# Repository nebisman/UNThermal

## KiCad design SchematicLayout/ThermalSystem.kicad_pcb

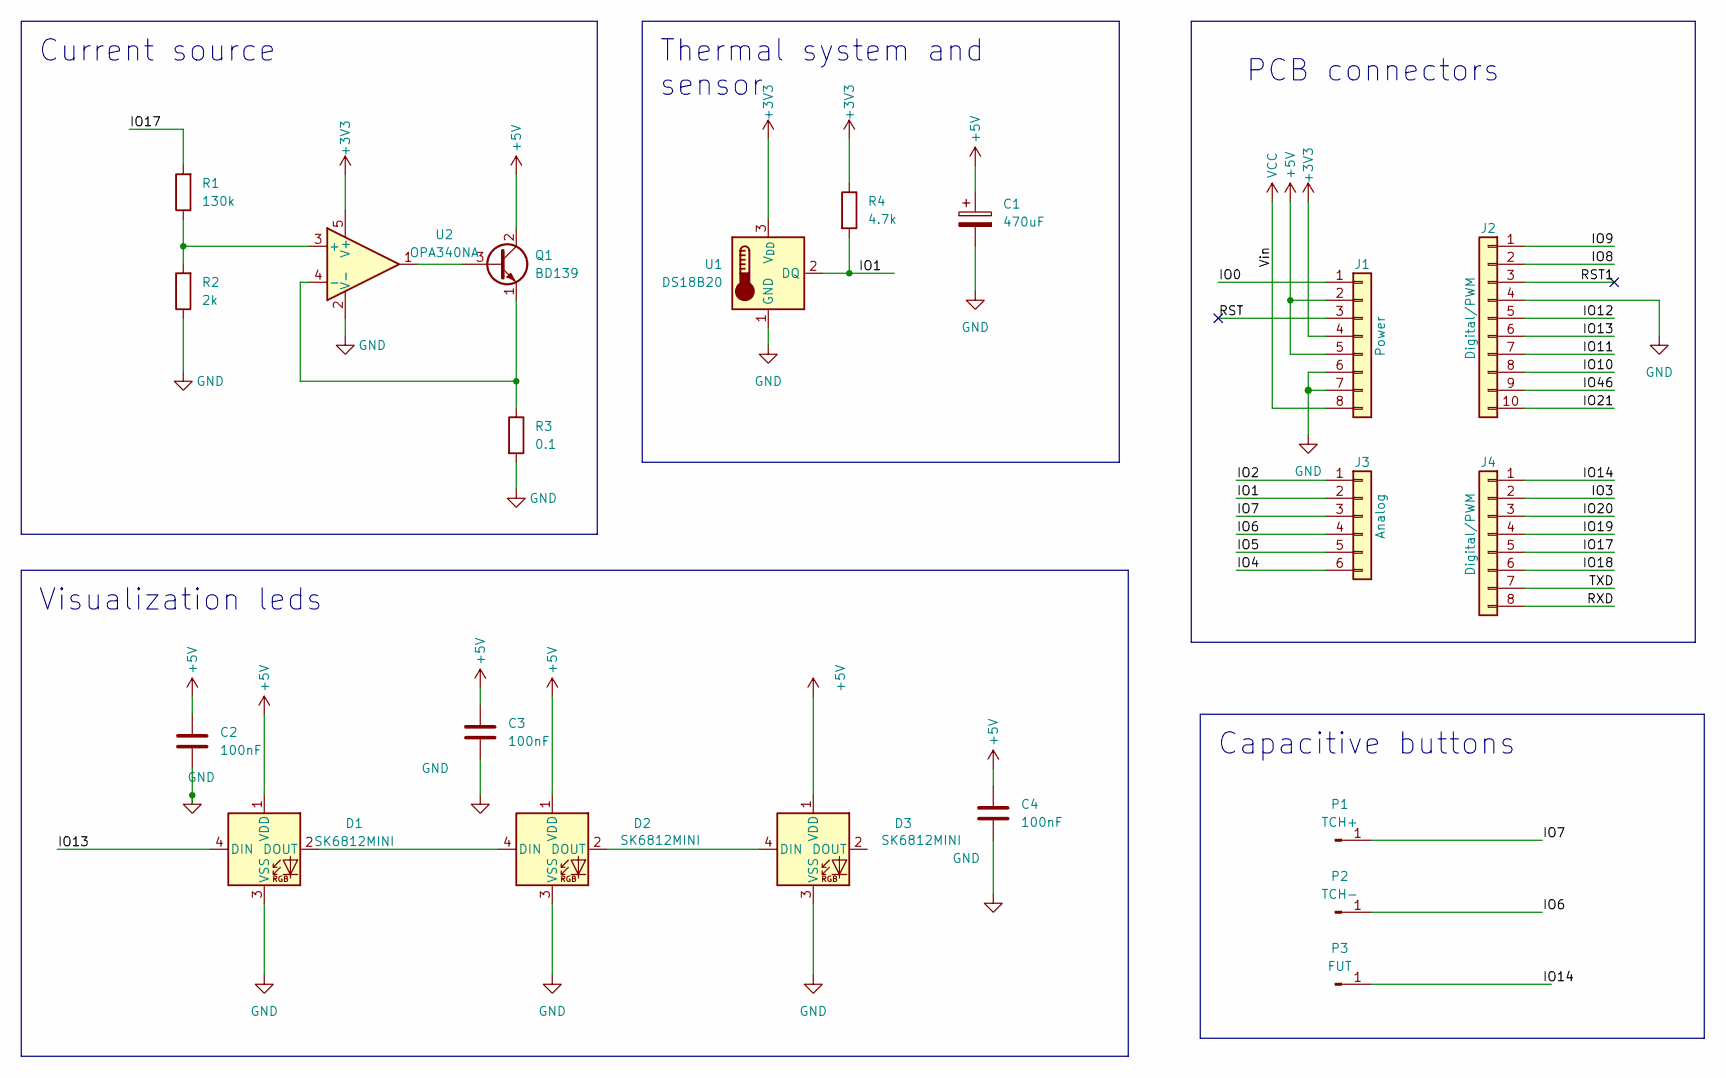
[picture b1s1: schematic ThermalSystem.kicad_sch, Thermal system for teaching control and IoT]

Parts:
C1: 470uF; CP_EIA-7343-30_AVX-N_Pad2.25x2.55mm_HandSolder
C2, C3, C4: 100nF; C_0805_2012Metric_Pad1.18x1.45mm_HandSolder
D1, D2, D3: SK6812MINI; LED_SK6812MINI_PLCC4_3.5x3.5mm_P1.75mm
J1: Power; PinSocket_1x08_P2.54mm_Vertical
J2: Digital/PWM; PinSocket_1x10_P2.54mm_Vertical
J3: Analog; PinSocket_1x06_P2.54mm_Vertical
J4: Digital/PWM; PinSocket_1x08_P2.54mm_Vertical
P1: TCH+; MountingHole_5mm_Pad_TopOnly
P2: TCH-; MountingHole_5mm_Pad_TopOnly
P3: FUT; MountingHole_5mm_Pad_TopOnly
Q1: BD139; TO-126-3_Vertical
R1: 130k; R_0805_2012Metric_Pad1.20x1.40mm_HandSolder
R2: 2k; R_0805_2012Metric_Pad1.20x1.40mm_HandSolder
R3: 0.1; R_0805_2012Metric_Pad1.20x1.40mm_HandSolder
R4: 4.7k; R_0805_2012Metric_Pad1.20x1.40mm_HandSolder
U1: DS18B20; TO-92_Inline
U2: OPA340NA; SOT-23-5

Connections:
+3V3: J1.4, R4.1, U1.3 (V_{DD}), U2.5 (V+)
+5V: C1.1, C2.1, C3.1, C4.1, D1.1 (VDD), D2.1 (VDD), D3.1 (VDD), J1.2, J1.5, Q1.2 (C)
/IO0: J1.1
/IO1: J3.2, R4.2, U1.2 (DQ)
/IO2: J3.1
/IO3: J4.2
/IO4: J3.6
/IO5: J3.5
/IO6: J3.4, P2.1
/IO7: J3.3, P1.1
/IO8: J2.2
/IO9: J2.1
/IO10: J2.8
/IO11: J2.7
/IO12: J2.5
/IO13: D1.4 (DIN), J2.6
/IO14: J4.1, P3.1
/IO17: J4.5, R1.2
/IO18: J4.6
/IO19: J4.4
/IO20: J4.3
/IO21: J2.10
/IO46: J2.9
/RST: J1.3
/RST1: J2.3
/RXD: J4.8
/TXD: J4.7
GND: C1.2, C2.2, C3.2, C4.2, D1.3 (VSS), D2.3 (VSS), D3.3 (VSS), J1.6, J1.7, J2.4, R2.1, R3.2, U1.1 (GND), U2.2 (V-)
unnamed: D1.2 (DOUT), D2.4 (DIN)
unnamed: D2.2 (DOUT), D3.4 (DIN)
unnamed: Q1.3 (B), U2.1
unnamed: Q1.1 (E), R3.1, U2.4 (-)
unnamed: R1.1, R2.2, U2.3 (+)
VCC: J1.8

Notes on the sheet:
Visualization leds
Capacitive buttons
Thermal system and sensor
Current source
PCB connectors

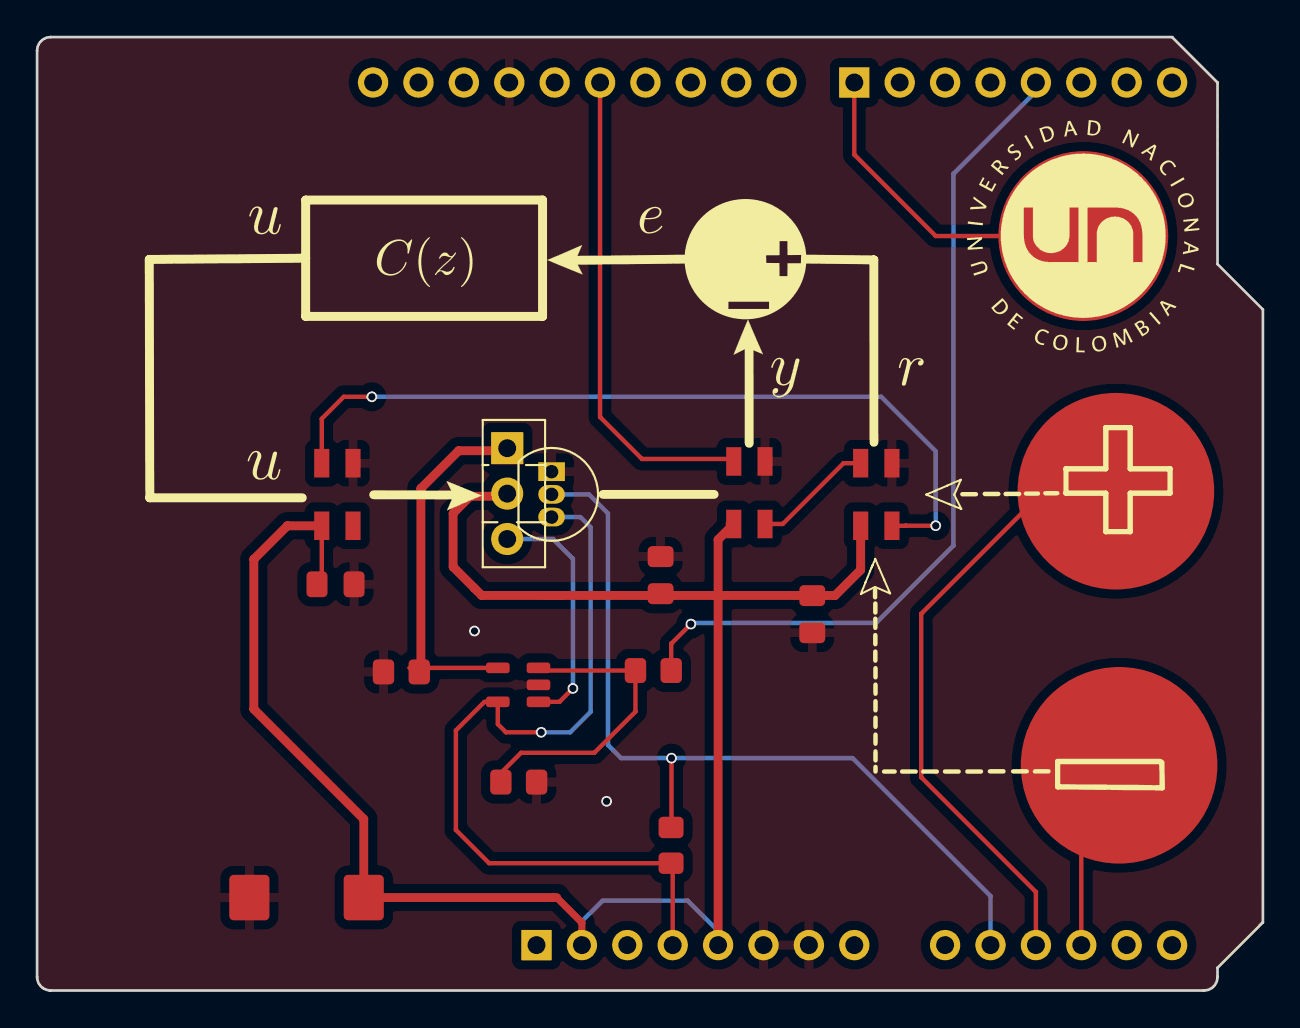
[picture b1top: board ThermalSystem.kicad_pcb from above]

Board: 2 copper layers, 68.6 x 53.3 mm, 21 parts (0 on the bottom side), 14 nets.

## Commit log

2025-05-19 guia 1 modificada
2025-05-27 guia 3 agregada
2025-05-27 guia 2 modificada
2025-05-27 guia 3 modificada
2025-05-27 Revert "guia 3 modificada"
    This reverts commit cafdbc8fb09101462f5ea5dfb9794f50a4172436.
2025-09-02 guia 1 updated
2025-09-16 guia 2 updated
2025-09-30 guia 3 updated
2025-09-30 tuning PID updated
2026-01-15 diagram updated
2026-01-15 notebook example updated
2026-02-03 guia de instalacion
2026-02-03 cambiado
2026-02-09 guide 1 2026 updated
2026-03-10 guide 3 2026 updated
